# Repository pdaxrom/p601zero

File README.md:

## Pyldin-601 compatible retrocomputer.

[History](docs/HISTORY.md)

### Overview hardware version 1.2:

 Function | Description 
----|----
CPU | [System 11 - VHDL 68HC11](http://members.optusnet.com.au/jekent/system11/)
FPGA| [Lattice MachXO2-4000HC module](http://www.stepfpga.com)
RAM | Builtin FPGA 4KB and/or external static ram 128KB
ROM | Builtin FPGA BOOTROM 2KB
Keyboard | PS/2
Serial port | UART (via keyboard connector)
Video | TV (b/w)
Audio | AY-3-8912
Storage | MMC/SD
Other | Onboard SPI and CS ports, 8 bit parallel port (limited to output only)

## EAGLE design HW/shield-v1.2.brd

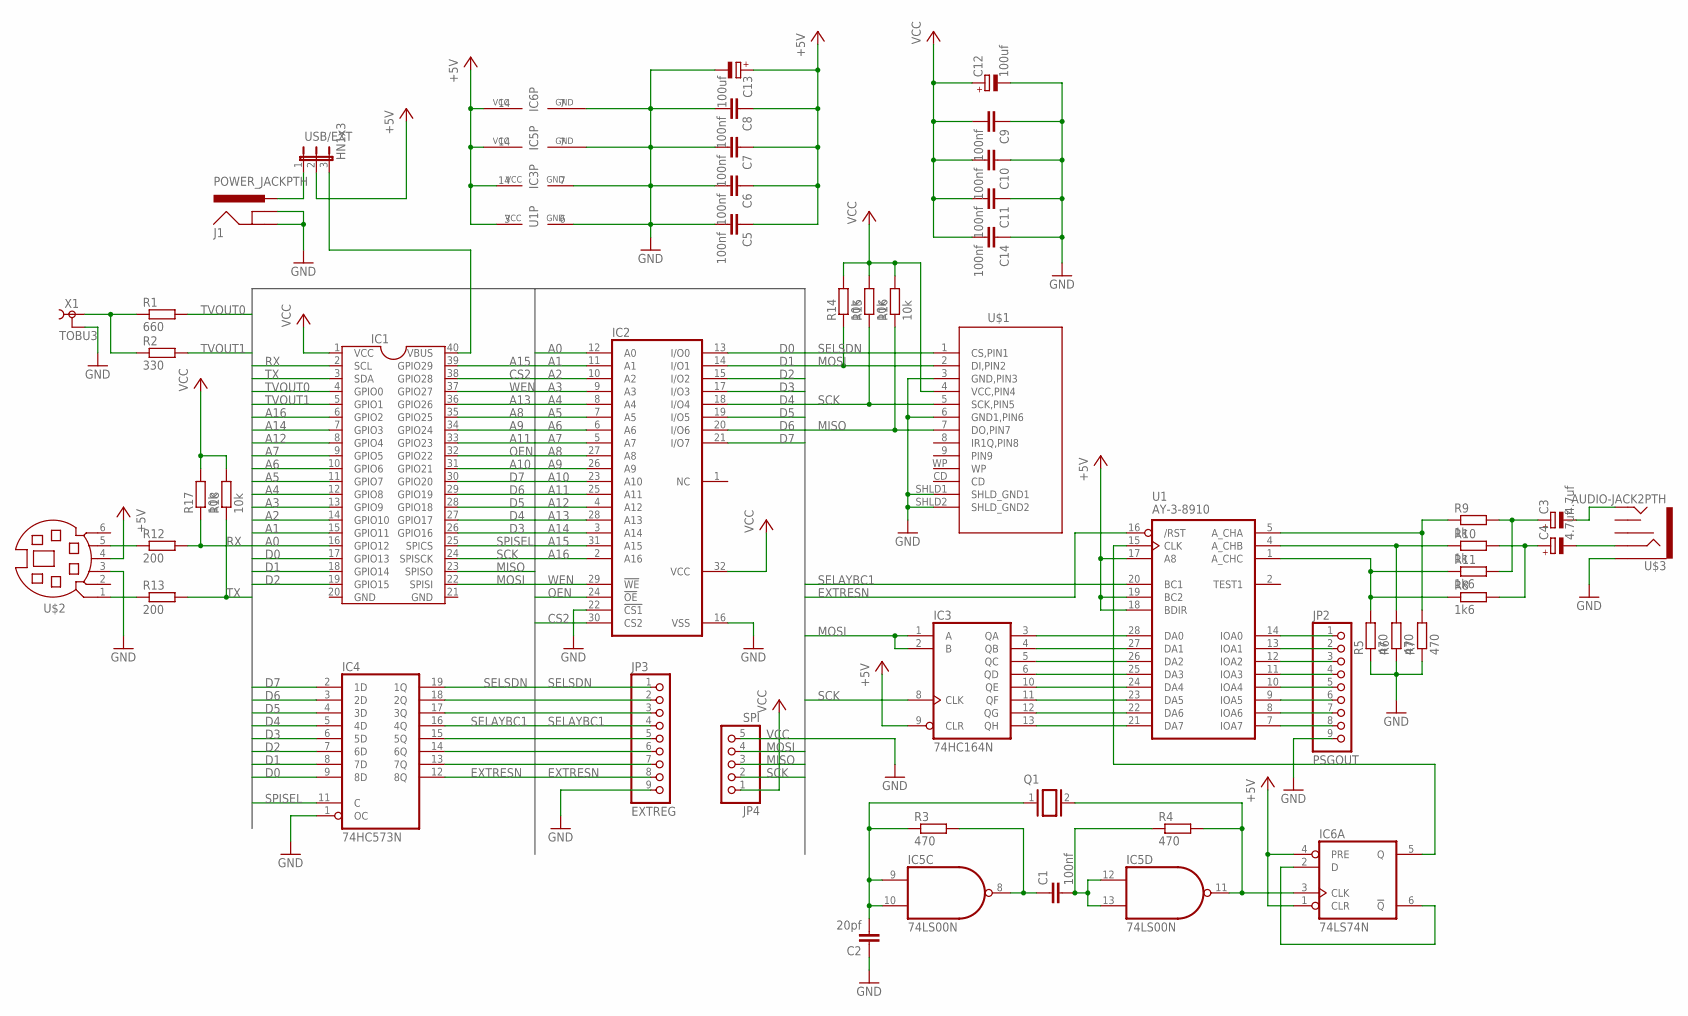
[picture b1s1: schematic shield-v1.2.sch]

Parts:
C1, C5, C6, C7, C8, C9, C10, C11, C14: 100nf; 1206
C2: 20pf; 1206
C3, C4: 4.7uf; E5-5
C12, C13: 100uf; E5-5
IC1: STEPFPGA; DIL40
IC2: 628128P; DIL32
IC3: 74HC164N; DIL14
IC4: 74HC573N; DIL20
IC5: 74LS00N; DIL14
IC6: 74LS74N; DIL14
J1: POWER_JACKPTH; POWER_JACK_PTH
JP2: PSGOUT; 1X09
JP3: EXTREG; 1X09
JP4: SPI; 1X05
Q1: XTAL/S; QS
R1: 660; R1206
R2: 330; R1206
R3, R4, R5, R6, R7: 470; R1206
R8, R11: 1k6; R1206
R9, R10: 1k; R1206
R12, R13: 200; R1206
R14, R15, R16, R17, R18: 10k; R1206
U1: AY-3-8910; DIL28-6
U$1: FCI_SD_SOCKET; SD-MMC_SOCKET-PP
U$2: MD06SS; MDIN06SS
U$3: AUDIO-JACK2PTH; AUDIO-JACK
USB/EXT: HN1x3; JP2
X1: TOBU3

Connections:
+5V: C5.1, C6.1, C7.1, C8.1, C13.+, IC3.9 (CLR), IC3.14 (VCC), IC5.14 (VCC), IC6.1 (CLR), IC6.4 (PRE), IC6.14 (VCC), U1.3 (VCC), U1.17 (A8), U1.18 (BDIR), U1.19 (BC2), U$2.4, USB/EXT.2
A0: IC1.16 (GPIO12), IC2.12 (A0)
A1: IC1.15 (GPIO11), IC2.11 (A1)
A2: IC1.14 (GPIO10), IC2.10 (A2)
A3: IC1.13 (GPIO9), IC2.9 (A3)
A4: IC1.12 (GPIO8), IC2.8 (A4)
A5: IC1.11 (GPIO7), IC2.7 (A5)
A6: IC1.10 (GPIO6), IC2.6 (A6)
A7: IC1.9 (GPIO5), IC2.5 (A7)
A8: IC1.35 (GPIO25), IC2.27 (A8)
A9: IC1.34 (GPIO24), IC2.26 (A9)
A10: IC1.31 (GPIO21), IC2.23 (A10)
A11: IC1.33 (GPIO23), IC2.25 (A11)
A12: IC1.8 (GPIO4), IC2.4 (A12)
A13: IC1.36 (GPIO26), IC2.28 (A13)
A14: IC1.7 (GPIO3), IC2.3 (A14)
A15: IC1.39 (GPIO29), IC2.31 (A15)
A16: IC1.6 (GPIO2), IC2.2 (A16)
CS2: IC1.38 (GPIO28), IC2.30 (CS2)
D0: IC1.17 (GPIO13), IC2.13 (I/O0), IC4.9 (8D)
D1: IC1.18 (GPIO14), IC2.14 (I/O1), IC4.8 (7D)
D2: IC1.19 (GPIO15), IC2.15 (I/O2), IC4.7 (6D)
D3: IC1.26 (GPIO16), IC2.17 (I/O3), IC4.6 (5D)
D4: IC1.27 (GPIO17), IC2.18 (I/O4), IC4.5 (4D)
D5: IC1.28 (GPIO18), IC2.19 (I/O5), IC4.4 (3D)
D6: IC1.29 (GPIO19), IC2.20 (I/O6), IC4.3 (2D)
D7: IC1.30 (GPIO20), IC2.21 (I/O7), IC4.2 (1D)
EXTRESN: IC4.12 (8Q), JP3.8, U1.16 (/RST)
GND: C2.1, C5.2, C6.2, C7.2, C8.2, C9.1, C10.1, C11.1, C12.-, C13.-, C14.1, IC1.20 (GND), IC1.21 (GND), IC2.16 (VSS), IC2.22 (!CS1), IC3.7 (GND), IC4.1 (OC), IC4.10 (GND), IC5.7 (GND), IC6.7 (GND), J1.GND, J1.GNDBREAK, JP2.9, JP3.9, JP4.5, R5.1, R6.1, R7.1, U1.6 (GND), U$1.3 (GND,PIN3), U$1.6 (GND1,PIN6), U$1.SHLD1 (SHLD_GND1), U$1.SHLD2 (SHLD_GND2), U$2.3, U$3.SLEEVE, X1.2, X1.2@1 (2), X1.2@2 (2)
MISO: IC1.23 (SPISO), JP4.3, R16.1, U$1.7 (DO,PIN7)
MOSI: IC1.22 (SPISI), IC3.1 (A), IC3.2 (B), JP4.4, R14.1, U$1.2 (DI,PIN2)
unnamed: R1.1, R2.1, X1.1
unnamed: IC3.3 (QA), U1.28 (DA0)
unnamed: IC3.4 (QB), U1.27 (DA1)
unnamed: IC3.5 (QC), U1.26 (DA2)
unnamed: IC3.6 (QD), U1.25 (DA3)
unnamed: IC3.10 (QE), U1.24 (DA4)
unnamed: IC3.11 (QF), U1.23 (DA5)
unnamed: IC3.12 (QG), U1.22 (DA6)
unnamed: IC3.13 (QH), U1.21 (DA7)
unnamed: R5.2, R8.1, R11.1, U1.1 (A_CHC)
unnamed: C1.1, IC5.8 (O), R3.2
unnamed: C1.2, IC5.12 (I0), IC5.13 (I1), R4.1
unnamed: C2.2, IC5.9 (I0), IC5.10 (I1), Q1.1, R3.1
unnamed: IC5.11 (O), IC6.3 (CLK), Q1.2, R4.2
unnamed: R6.2, R10.1, U1.4 (A_CHB)
unnamed: IC6.2 (D), IC6.6 (!Q)
unnamed: IC6.5 (Q), U1.15 (CLK)
unnamed: R7.2, R9.1, U1.5 (A_CHA)
unnamed: C4.+, R8.2, R10.2
unnamed: C3.+, R9.2, R11.2
unnamed: C3.-, U$3.TIP
unnamed: C4.-, U$3.RING
unnamed: R12.1, U$2.5
unnamed: R13.1, U$2.1
unnamed: JP2.1, U1.14 (IOA0)
unnamed: JP2.2, U1.13 (IOA1)
unnamed: JP2.3, U1.12 (IOA2)
unnamed: JP2.4, U1.11 (IOA3)
unnamed: JP2.5, U1.10 (IOA4)
unnamed: JP2.6, U1.9 (IOA5)
unnamed: JP2.7, U1.8 (IOA6)
unnamed: JP2.8, U1.7 (IOA7)
unnamed: IC4.18 (2Q), JP3.2
unnamed: IC4.17 (3Q), JP3.3
unnamed: IC4.15 (5Q), JP3.5
unnamed: IC4.14 (6Q), JP3.6
unnamed: IC4.13 (7Q), JP3.7
unnamed: J1.PWR, USB/EXT.1
unnamed: IC1.40 (VBUS), USB/EXT.3
OEN: IC1.32 (GPIO22), IC2.24 (!OE)
RX: IC1.2 (SCL), R12.2, R17.1
SCK: IC1.24 (SPISCK), IC3.8 (CLK), JP4.2, R15.1, U$1.5 (SCK,PIN5)
SELAYBC1: IC4.16 (4Q), JP3.4, U1.20 (BC1)
SELSDN: IC4.19 (1Q), JP3.1, U$1.1 (CS,PIN1)
SPISEL: IC1.25 (SPICS), IC4.11 (C)
TVOUT0: IC1.4 (GPIO0), R1.2
TVOUT1: IC1.5 (GPIO1), R2.2
TX: IC1.3 (SDA), R13.2, R18.1
VCC: C9.2, C10.2, C11.2, C12.+, C14.2, IC1.1 (VCC), IC2.32 (VCC), IC4.20 (VCC), JP4.1, R14.2, R15.2, R16.2, R17.2, R18.2, U$1.4 (VCC,PIN4)
WEN: IC1.37 (GPIO27), IC2.29 (!WE)

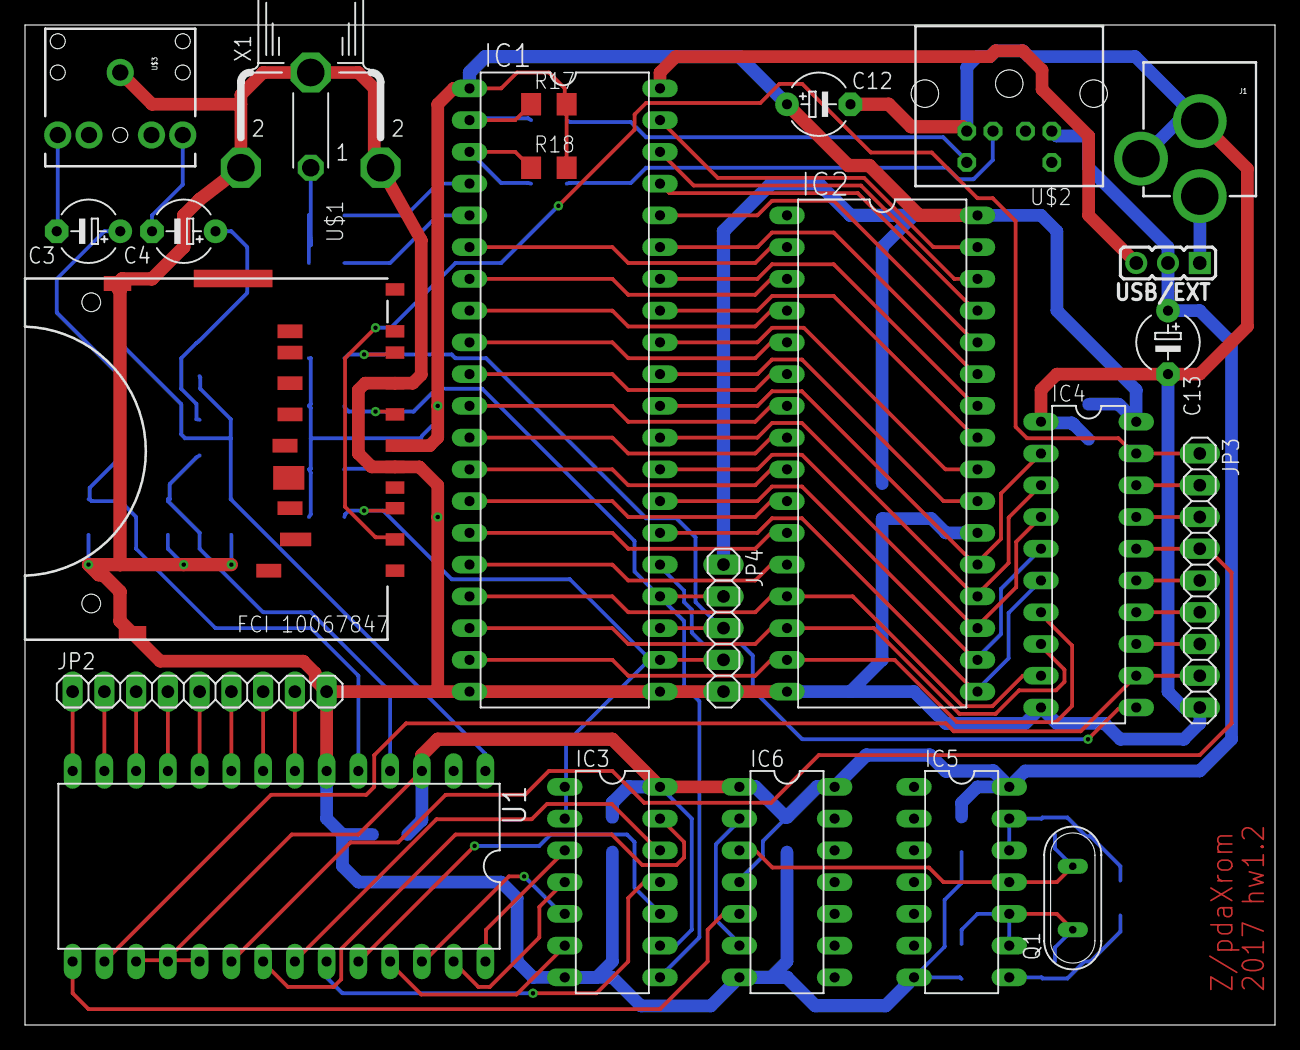
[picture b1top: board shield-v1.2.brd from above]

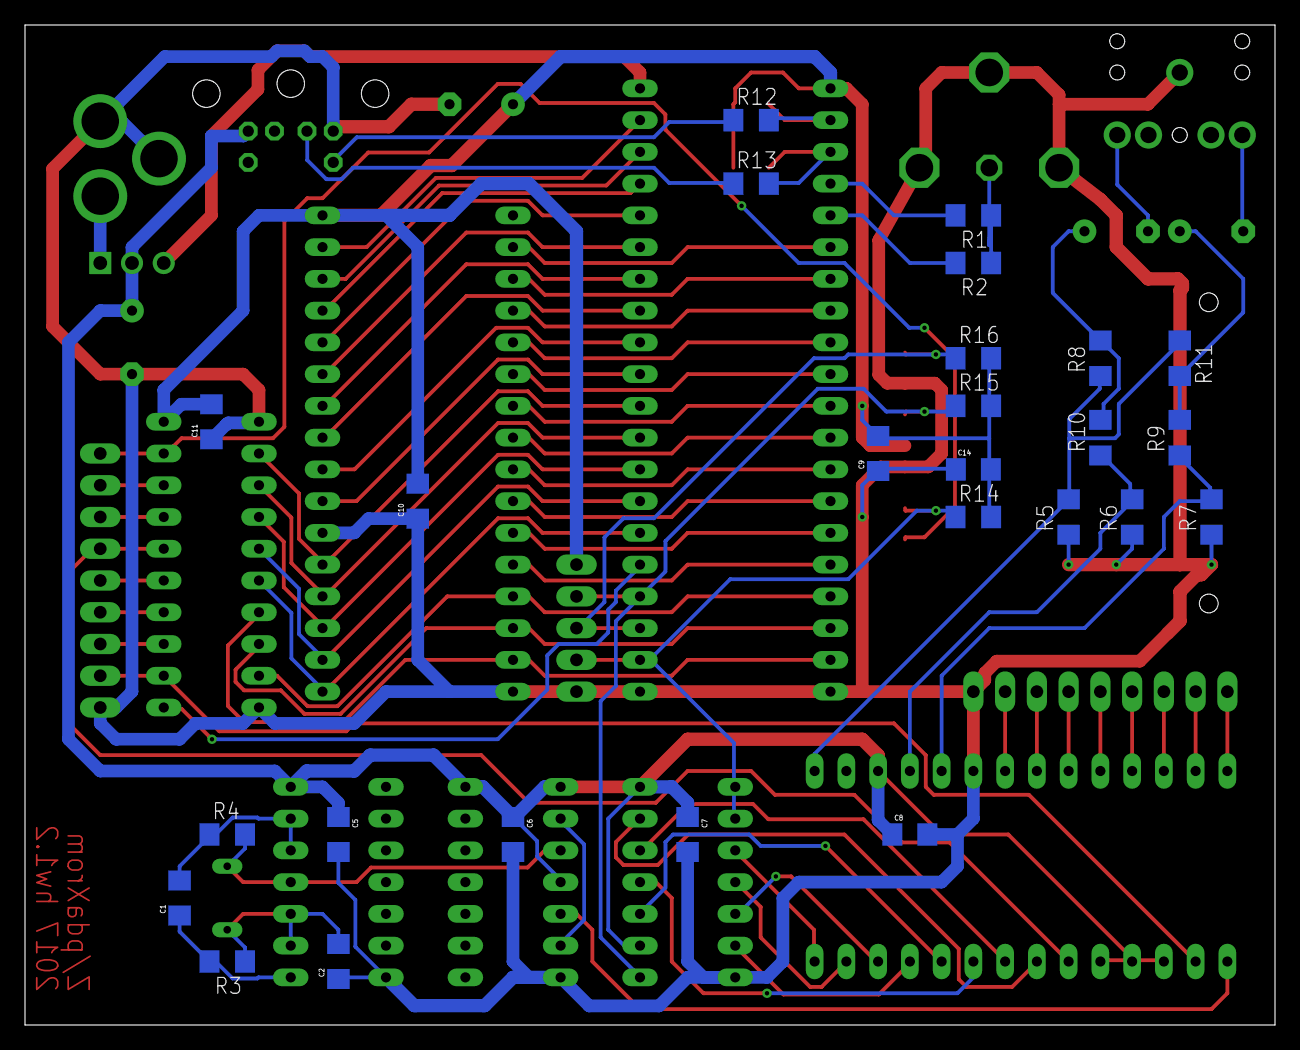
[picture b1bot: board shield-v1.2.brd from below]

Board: 2 copper layers, 100.0 x 80.0 mm, 49 parts (26 on the bottom side), 81 nets.

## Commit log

2017-04-07 lattice mach xo2 hardware
2017-04-07 remove programmer
2017-04-16 uart initial
2017-04-16 fix clock
2017-04-16 create verilog rom file
2017-04-16 clock reworking
2017-05-06 rx uart module
2017-05-06 RX error added to status register
2017-05-06 tx uart implementation
2017-05-06 added missed VMA signal
2017-05-06 vma?
2017-05-06 fix uart
2017-05-07 added programmable timer to simpleio, irq. uart removed from simpleio to separate module
2017-05-07 boot ram module updated
2017-05-07 updated project
2017-05-07 remove old sources
2017-05-11 working uart rx/tx
2017-05-12 device map include file
2017-05-12 uartio rx/tx interrupt support initial
2017-05-12 uart interrupts
2017-05-12 fixed warnings and interrupt flags
2017-05-12 2048 bytes onboard ram
2017-05-12 bootrom and bootloader
2017-05-12 set default uart speed to 115200
2017-05-12 go command
2017-05-13 remove old tests
2017-05-13 added xgdx instruction
2017-05-13 cleanup xgdx code
2017-05-13 optimization for bootrom, hexout function added
2017-05-13 rules for compile cmd binaries
2017-05-13 4KB builtin RAM
2017-05-14 irq demo
2017-05-14 notes
2017-05-14 UART DEMO, MICROBASIC
2017-05-14 fixed chars printed to terminal
2017-05-14 deps added
2017-05-15 MicroBasicPlus sources fixed for 6803 asm
2017-05-16 external sram interface
2017-05-16 ram check
2017-05-16 fixed microbasic plus
2017-05-18 fix ext clock to 24MHz
2017-05-18 tv out initial
2017-05-18 ram test
2017-05-19 external ram tests
2017-05-19 reworked for prototype board version 1
2017-05-19 videocrt initial
2017-05-19 fixed for booting in high memory
2017-05-20 builtin vram test
2017-05-20 framebuffer
2017-05-20 working linear framebuffer
2017-05-21 page selector
2017-05-21 clear page lock
2017-05-22 page selector, linear framebuffer
2017-05-22 cleaned
2017-05-22 working pyldin fb (first byte still issued)
2017-05-22 fixed framebuffer
2017-05-22 text mode
2017-05-22 text mode test
2017-05-27 move to branches
2017-05-27 sd module, rampages
2017-05-29 MMC init
2017-05-29 added sd_read
2017-05-29 write to sd card
2017-05-29 sd flush
2017-05-30 fixed sram OEn and WEn
2017-05-30 24MHz system clk and 6MHz default CPU speed
2017-05-30 4KB version
2017-05-30 external sram buses renamed to external bus and sram_cs2
2017-05-30 simpleio timer clock is clk_in (24MHz)
2017-05-30 sdcard input clock is clk_in (24MHz)
2017-06-01 VPU software rastering test
2017-06-01 VPU initial
2017-06-02 16bit access to VPU
2017-06-02 vpu dma demo
2017-06-02 dma engine
2017-06-02 disable bram by default
2017-06-02 at least 3 nops must be after start the VPU DMA engine
2017-06-02 fix DMA start code
2017-06-02 nmi as video interrupt
2017-06-02 video driver for linear framebuffer
2017-06-02 fix black line render
2017-06-03 removed CPU register access to vpu line buffer, each dma transfer reset destination buffer address to VPU_ADDR value
2017-06-03 start, end vertical triggers for VPU
2017-06-03 VPU graphics/text mode
2017-06-03 text/graf demo
2017-06-03 vrom.v included
2017-06-04 interrupt vectors registers added to page selector device, ext/int ram detection added to BOOTROM
2017-06-04 AY-3-8912 port write
2017-06-05 spi select external register
2017-06-05 syncronous external bus access
2017-06-06 spi reset sygnal added
2017-06-07 simple YM3 player
2017-06-07 reset function
2017-06-07 fix clean
2017-06-08 ram wait cycles for VPU DMA engine
2017-06-10 stable 6 MHz, dymamical code commented
2017-06-14 Small C initial
2017-06-14 fix data size for addd and subd
2017-06-14 added eq and ne comparing
2017-06-14 le,ge,lt,gt comparison
2017-06-15 command line mode
2017-06-15 renamed
2017-06-15 exit status
2017-06-15 do, for
2017-06-15 unsigned 16bit divide
2017-06-15 fixes
2017-06-15 fix for functions
2017-06-15 casting initial
2017-06-16 char args pushed in stack as one byte
2017-06-16 more math
2017-06-16 pointer comparison
2017-06-16 more fixes for self compilation
2017-06-16 fix labels
2017-06-16 hex/oct numbers and special chrs
2017-06-16 gpio example
2017-06-16 test
2017-06-16 abi optimization, default int size for char args
2017-06-17 updated assembler, linker and library added
2017-06-17 export symbols
2017-06-17 generate nonrelocable code
2017-06-17 reorganization
2017-06-17 build devtools and clib
2017-06-17 fix uniasm path
2017-06-17 bootrom library added
2017-06-17 removed system related stuff
2017-06-17 startup code for C compiler
2017-06-17 export C headers for devices and bootrom
2017-06-17 C examples
2017-06-17 embedded examples (fix adress for executables)
2017-06-17 symbol with 10 chars
2017-06-17 C samples
2017-06-17 replace asm hex sign $ to 0x
2017-06-18 some optimization
2017-06-18 fix syncro
2017-06-18 interlace mode
2017-06-18 removed unused
2017-06-19 fix regnames, remove old sources
2017-06-19 VPU fixed, BOOTROM updated
2017-06-19 autoincrement char line counter on each vpu interrupt
2017-06-19 videorom moved to EBR, vpu cache generated from logic
2017-06-20 vpu cursor, bios int calls
2017-06-20 NMI/IRQ external lines control
2017-06-20 hw dma access to video buffer, text and graphics modes
2017-06-20 vpu vblank irq added
2017-06-20 removed unused stuff
2017-06-21 fixed bootrom calls
2017-06-21 int 12, 13, 14, 15, initial 22, 23 added.
2017-06-22 int22 control chars updated: 08, 09, 0a, 0c, 0d, 18, 1b, 1e, 7f
2017-06-22 psg write block added
2017-06-22 misc examples
2017-06-23 SRAM initialization
2017-06-23 fixed cs for builtin ram
2017-06-23 count sram reset cycles
2017-06-23 sd example renamed
2017-06-23 SD card IO fixed in ROM
2017-06-24 umul, udiv functions
2017-06-24 bootsector fat16
2017-06-24 SD boot sector
2017-07-09 board revision 1.1
2017-07-10 mirroring internal ram to - for booting without external
2017-07-10 removed cpu hold with clock stops
2017-07-11 Moved to 6811 core. Because CPX now use full flags for comparison, some old 6800 applications can work wrong
2017-07-15 fixed mistyped page4 indexed state
2017-07-16 as11 and buffalo
2017-07-18 external irq added
2017-07-18 pagesel registers updated
2017-07-18 booting from sd, buffalo kernel
2017-07-18 hw 1.2 - final for current schematic
2017-07-20 fix title
2017-07-20 pyldin 601 compatible bios
2017-07-25 ps2 keyboard port
2017-07-25 Text screen scroll
2017-07-25 changed syscalls
2017-07-25 ps/2 keyboard initial
2017-07-26 fixed read from keyboard
2017-07-26 SW4 UART/Keyboard port switch
2017-07-26 ZBIOS setvec/getvec functions
2017-07-27 setvec/getvec, zbios initial
2017-07-27 68hc11 opcodes added to uniasm (no bit operatons yet!)
2017-07-28 github pages
2017-07-28 Create CNAME
2017-07-28 Set theme jekyll-theme-hacker
2017-07-28 Set theme jekyll-theme-midnight
2017-07-28 Set theme jekyll-theme-minimal
2017-09-02 fat16 driver initial
2017-09-04 cluster calc

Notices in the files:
parts and their libraries:
SparkFun: Licensing: CC v3.0 Share-Alike You are welcome to use this library for commercial purposes.
